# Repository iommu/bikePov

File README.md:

# bikePov
A POV(Persistence Of Vision) bike wheel display

This is a small custom project to attempt to cheaply make an easy to use custom POV bike display for drawing custom LED images on bike wheels.

For more information visit https://iommu.xyz

Copyright @ Alex Carter (iommu) 2019

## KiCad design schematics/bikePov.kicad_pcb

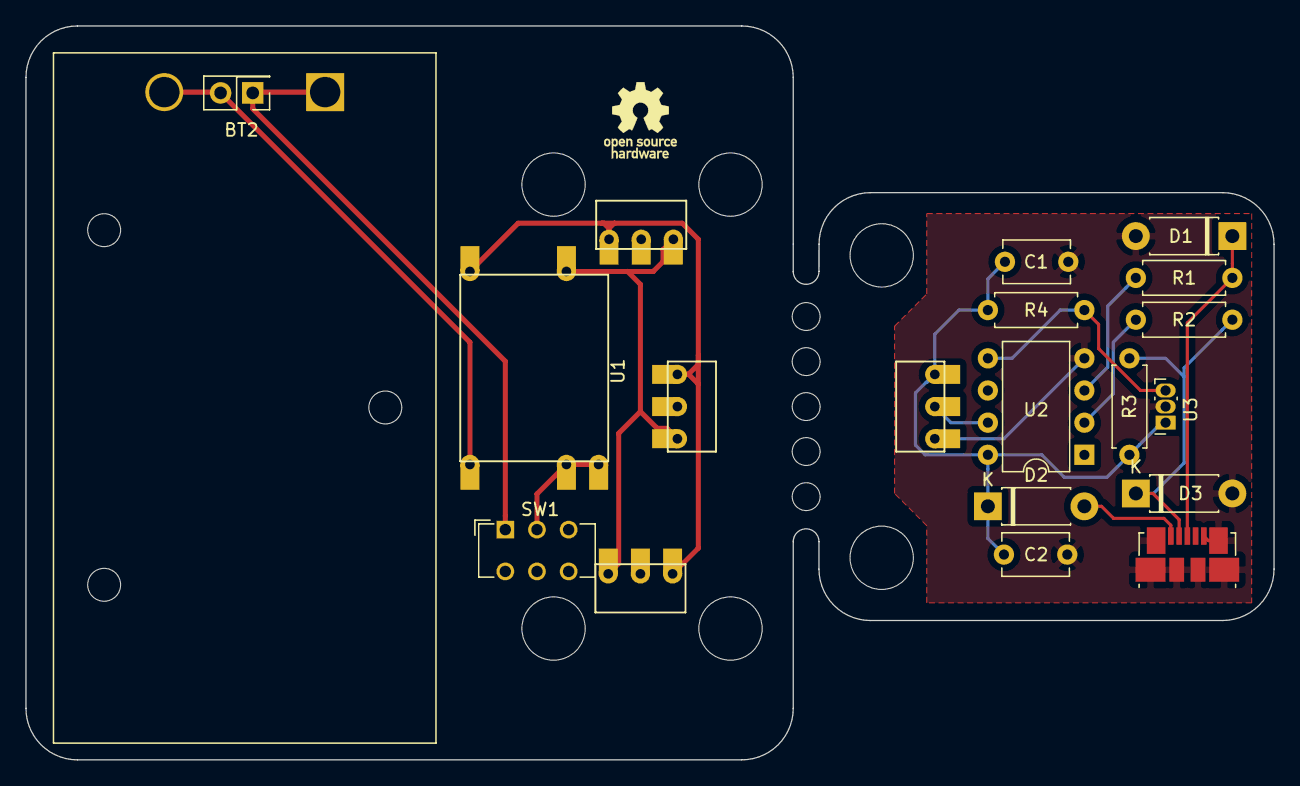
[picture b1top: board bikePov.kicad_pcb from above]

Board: 2 copper layers, 98.5 x 57.9 mm, 20 parts (0 on the bottom side), 14 nets.

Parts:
BT1: Battery; BatteryHolder_Eagle_12BH611-GR
BT2: Alt; PinHeader_2x01_P2.54mm_Vertical
C1: 4.7u; C_Disc_D5.1mm_W3.2mm_P5.00mm
C2: 0.1u; C_Disc_D5.1mm_W3.2mm_P5.00mm
D1, D3: 3.6 Zenner; D_DO-41_SOD81_P7.62mm_Horizontal
D2: 1N5817; D_DO-41_SOD81_P7.62mm_Horizontal
J1, J4, J5: WS2812 out; WS2812 strip
J2: WS2812 in; WS2812 strip
J3: Micro usb; USB_Micro-B_Molex_47346-0001
R1, R2: 68R; R_Axial_DIN0207_L6.3mm_D2.5mm_P7.62mm_Horizontal
R3: 1K5; R_Axial_DIN0207_L6.3mm_D2.5mm_P7.62mm_Horizontal
R4: 10K; R_Axial_DIN0207_L6.3mm_D2.5mm_P7.62mm_Horizontal
SW1: Power switch; SW_CuK_JS202011CQN_DPDT_Straight
U1: S09
U2: ATtiny85-20PU; DIP-8_W7.62mm
U3: Hall sensor; Allegro_SIP-3

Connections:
+5V: C1.2, C2.1, D2.1, J2.1, R3.2, R4.2, U2.8, U3.1
/D_in: J2.2, U2.7
/GND_in: J1.1, J4.1, J5.1, U1.1
/USB_M: R2.2, U2.2
/USB_P: R1.2, U2.3
/VCC_in: J1.3, J4.3, J5.3, U1.2
GND: C1.1, C2.2, D1.2, D3.2, J2.3, J3.5, J3.6, U2.4, U3.2
unnamed: BT1.1, BT2.1, SW1.1
unnamed: BT1.2, BT2.2, U1.3
unnamed: D1.1, J3.3, R1.1
unnamed: D2.2, J3.1
unnamed: D3.1, J3.2, R2.1, R3.1
unnamed: R4.1, U2.5, U3.3
unnamed: SW1.2, U1.4, U1.5

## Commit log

2019-07-26 First commit after completion of working PCB
2019-07-27 changed to camel case and updated PCB
